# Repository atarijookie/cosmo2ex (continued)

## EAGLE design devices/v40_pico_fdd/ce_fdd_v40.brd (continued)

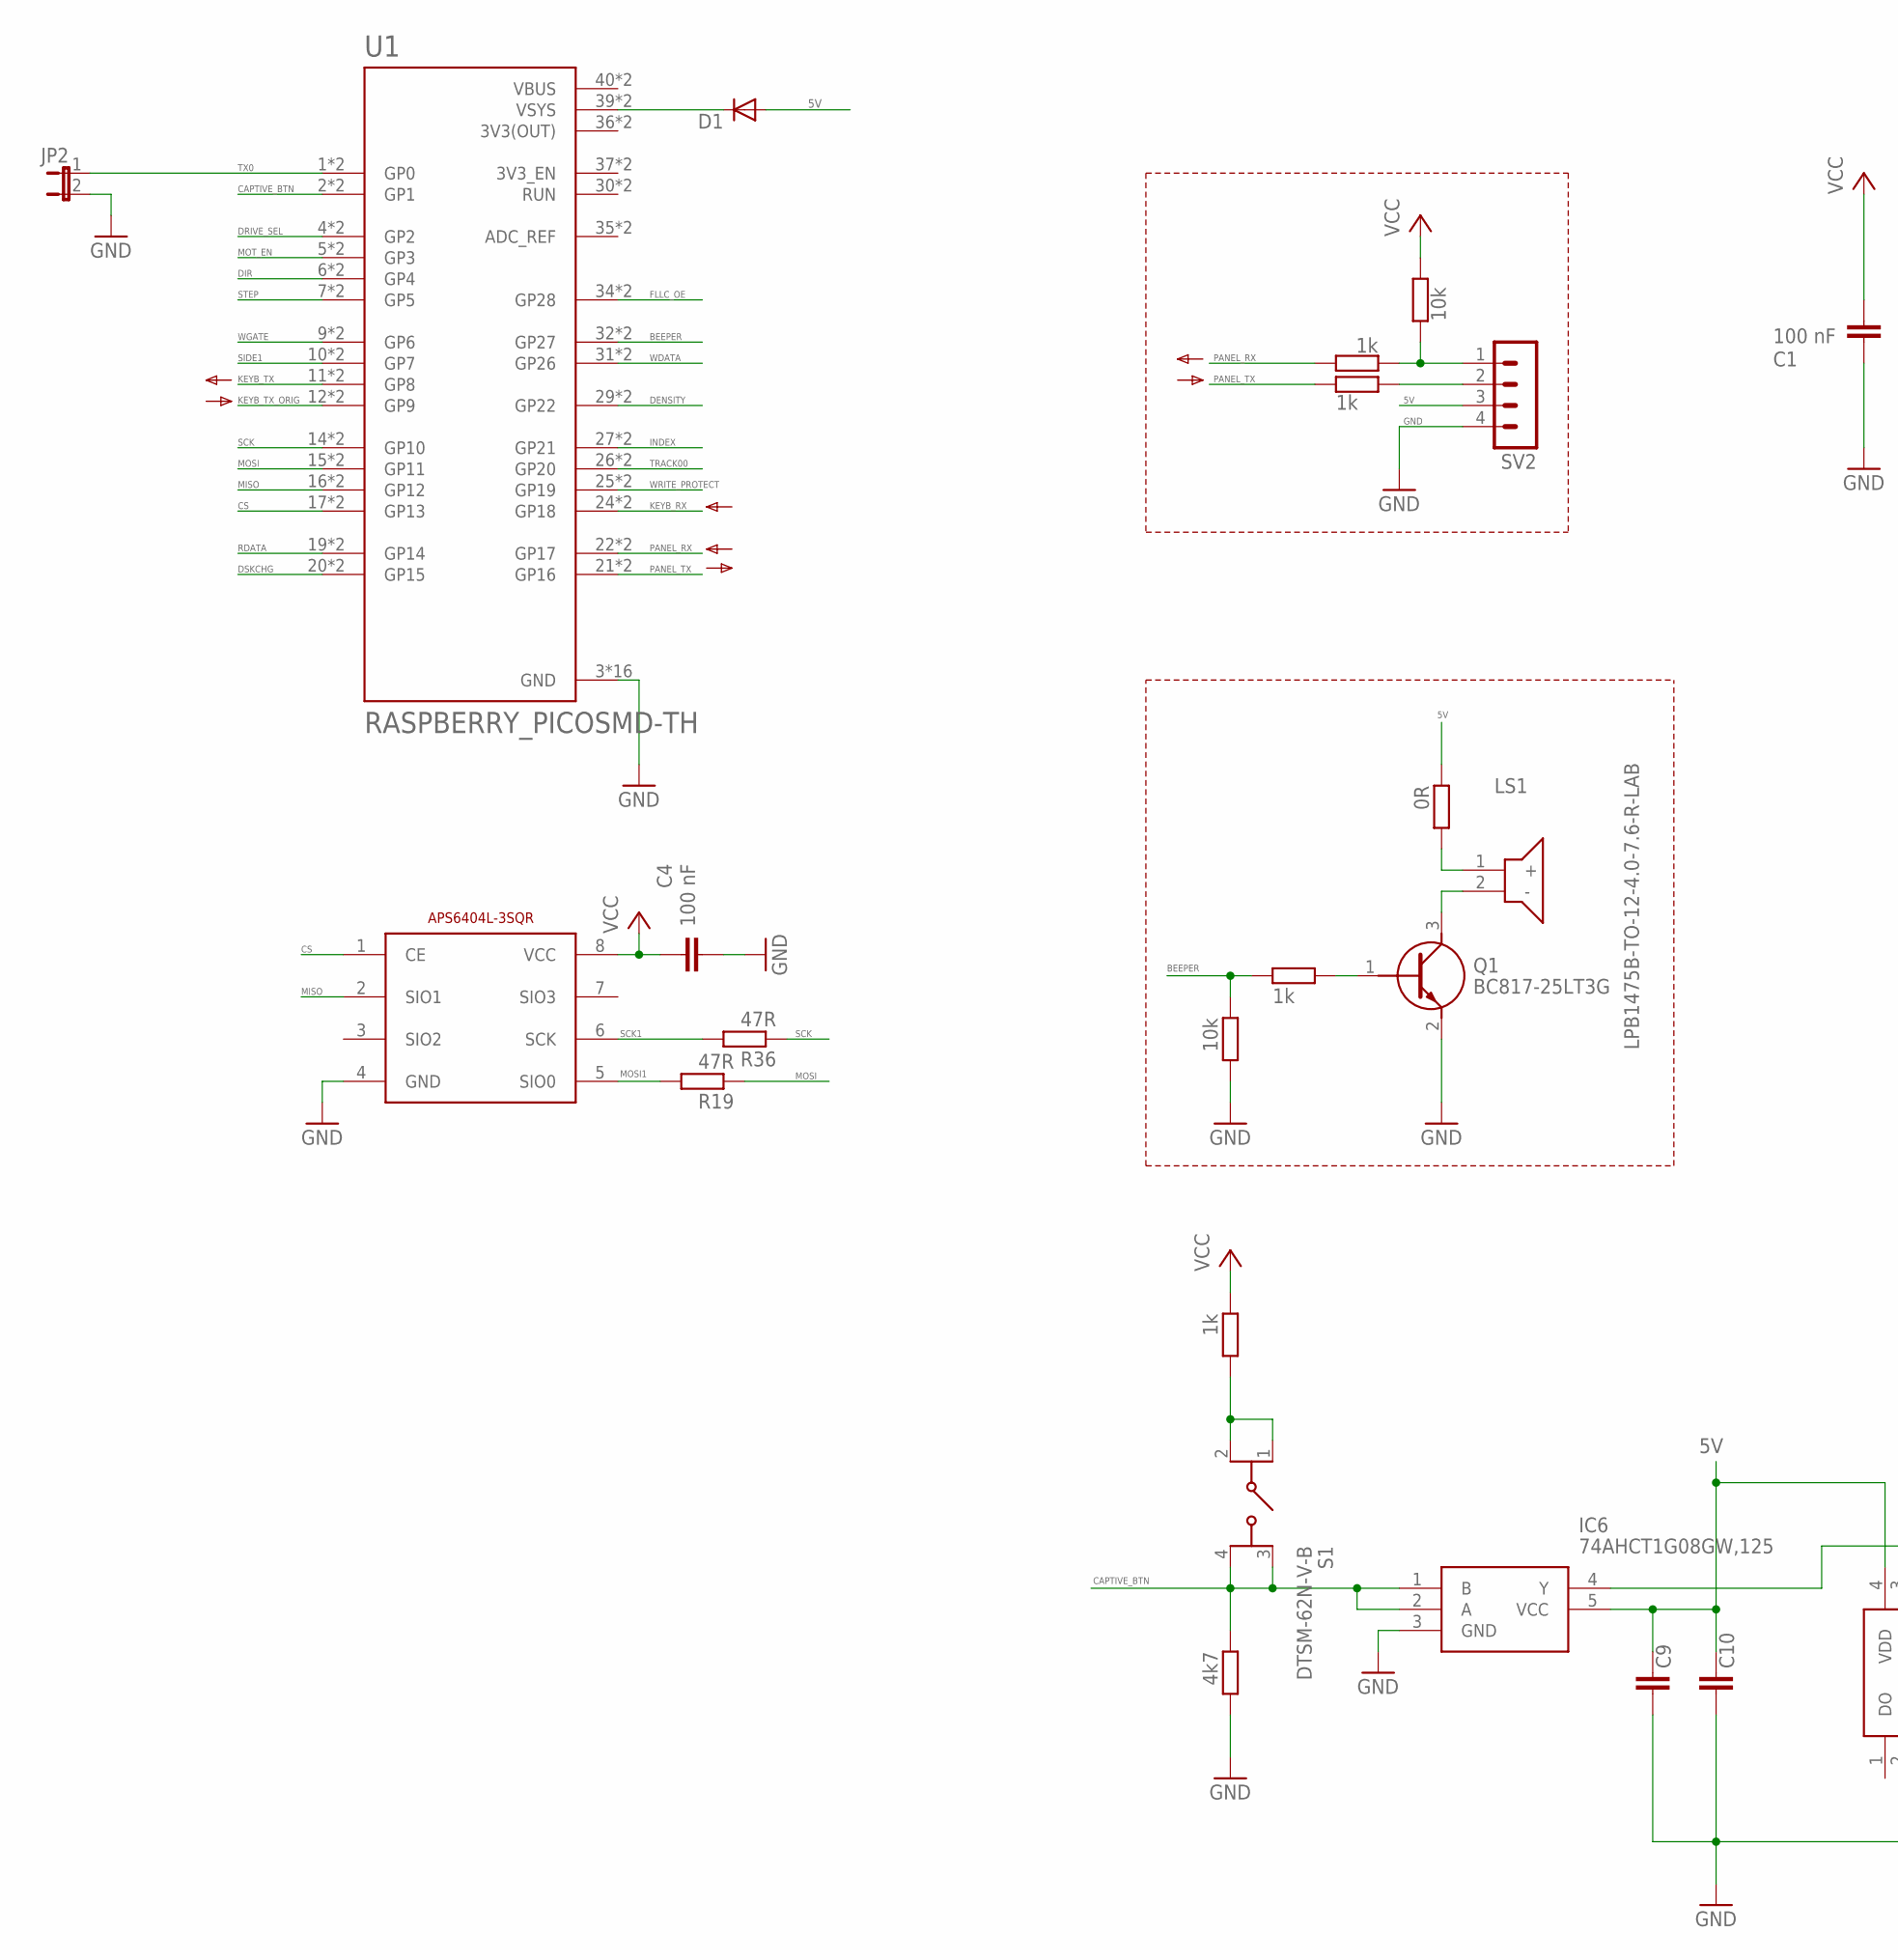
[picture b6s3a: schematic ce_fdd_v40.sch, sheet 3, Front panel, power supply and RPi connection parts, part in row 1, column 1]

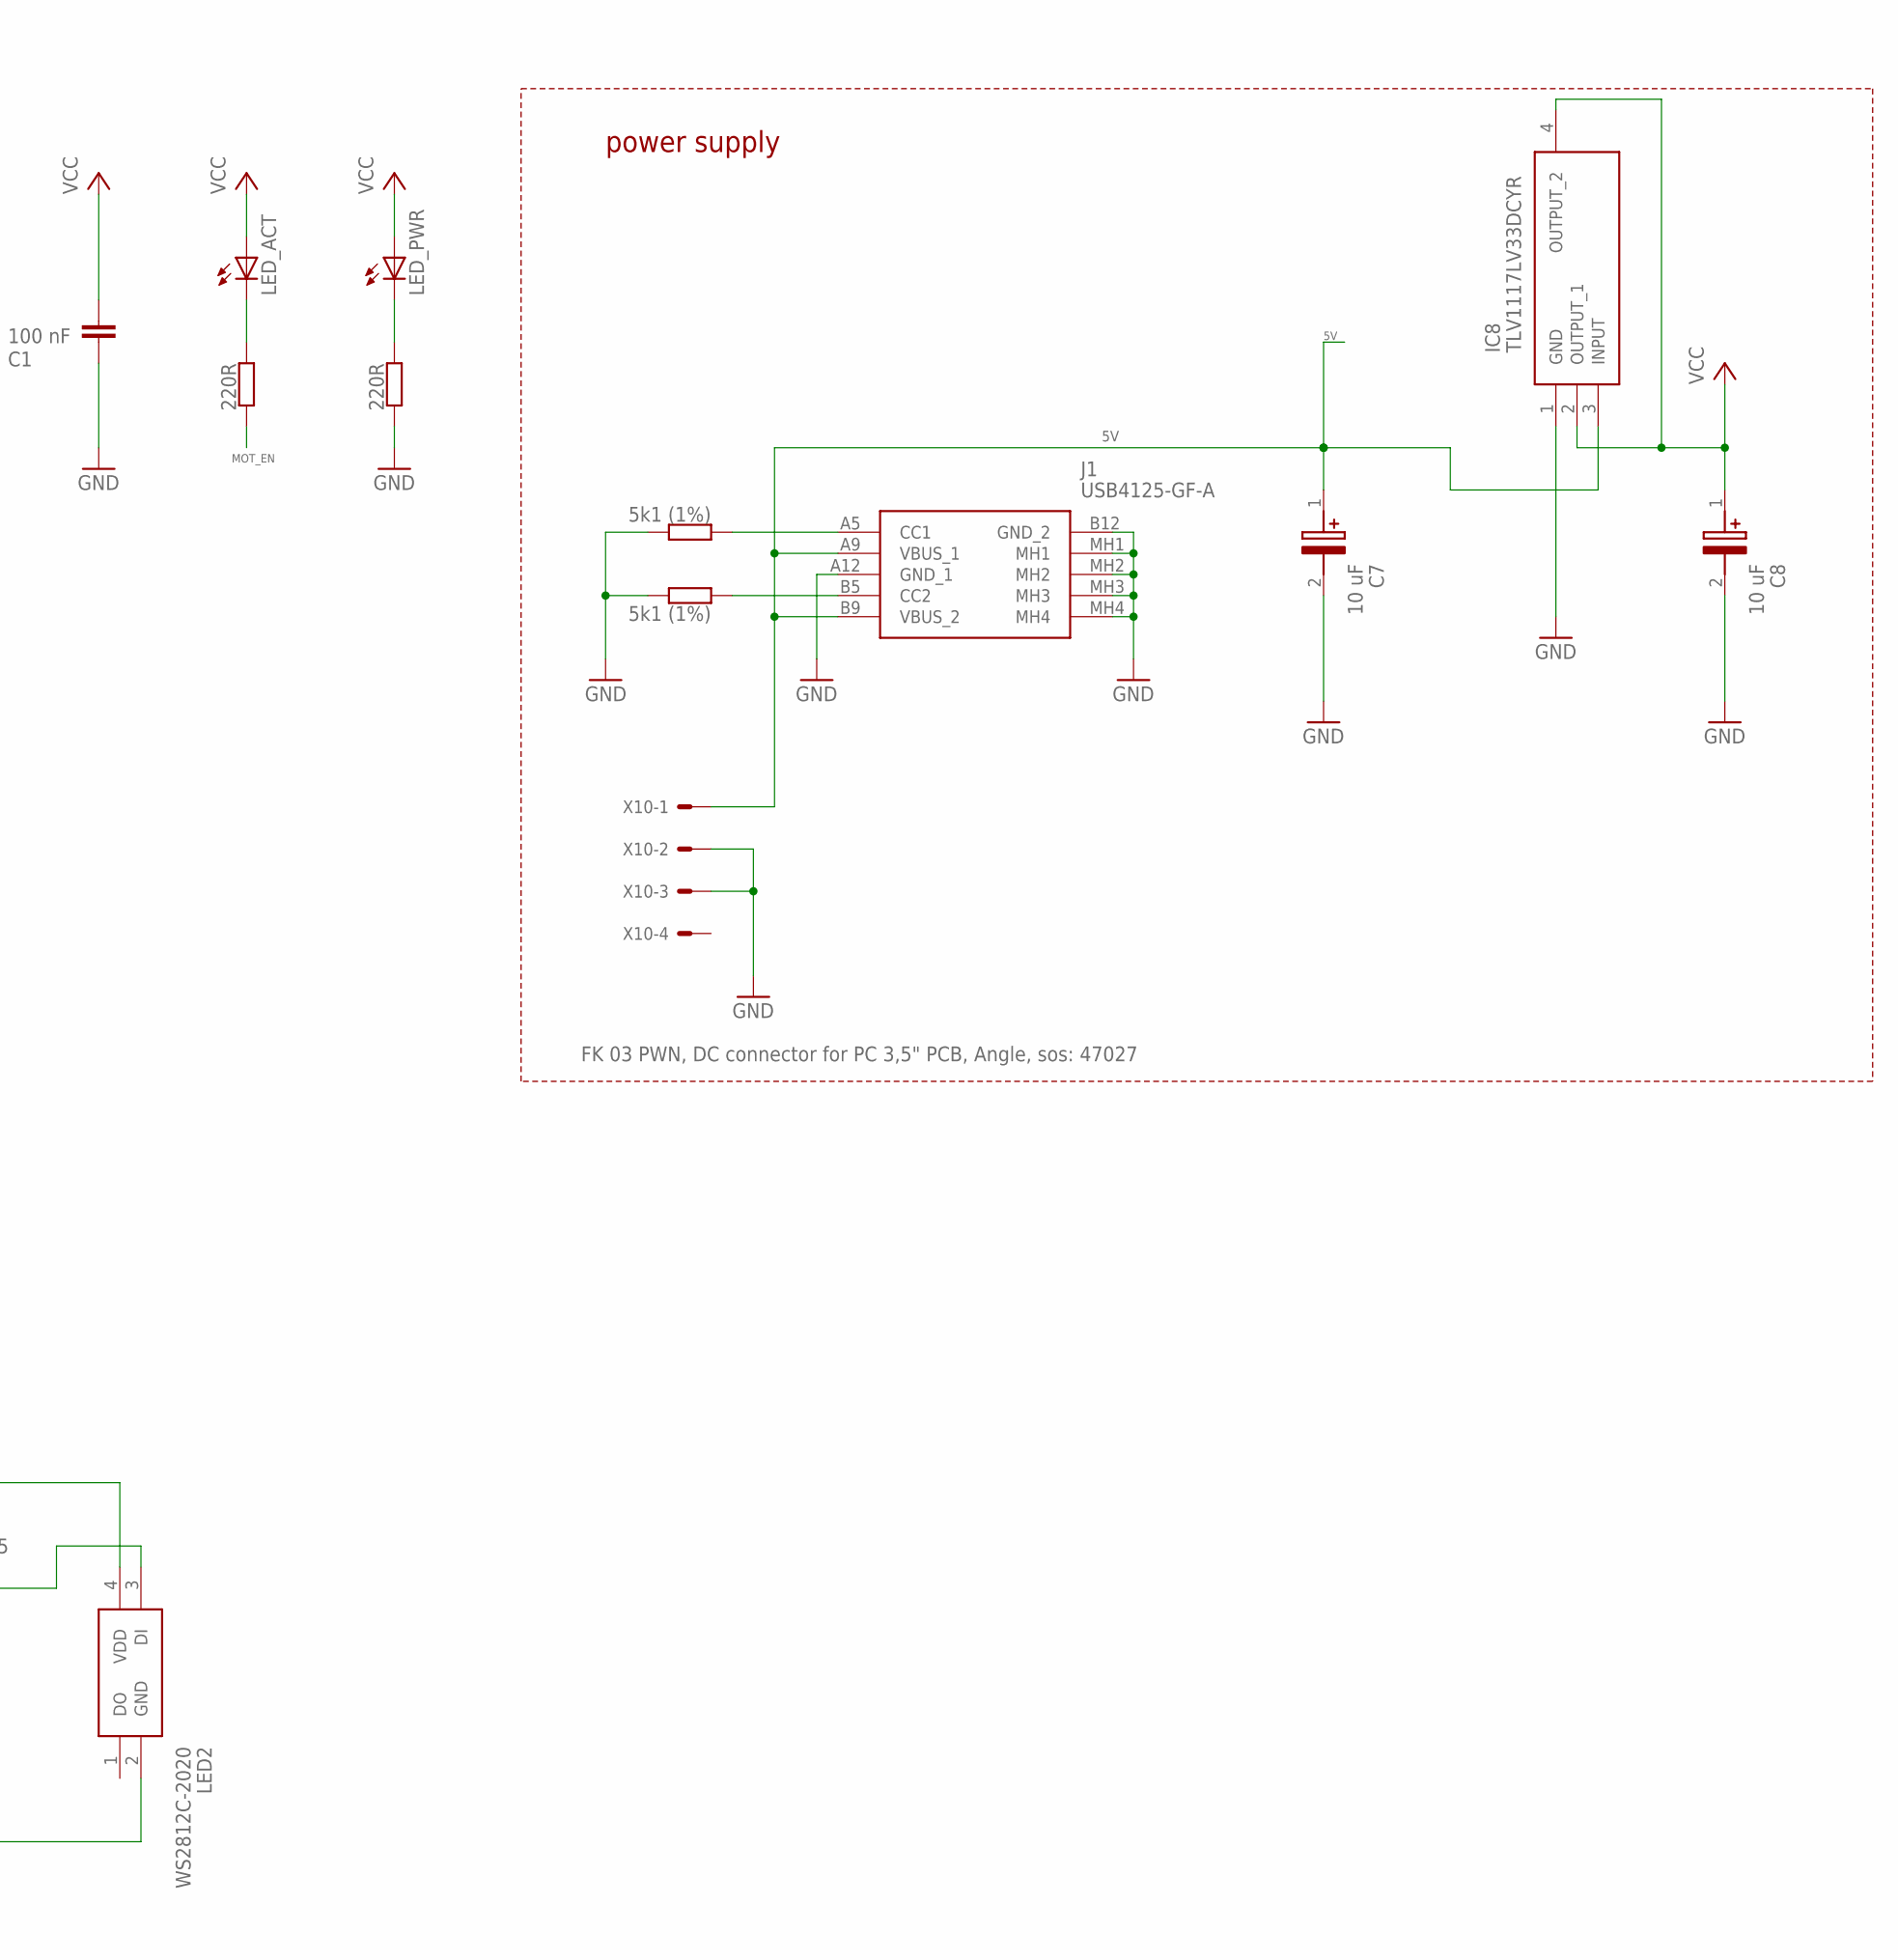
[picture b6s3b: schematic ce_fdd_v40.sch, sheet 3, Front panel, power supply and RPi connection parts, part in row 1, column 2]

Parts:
C1, C4, C9, C10: 100 nF; C0603
C7, C8: 10 uF; CAPPM3528X210N
D1: SK110-DIO; DO214AC
IC6: 74AHCT1G08GW,125; SOT65P212X110-5N
IC8: TLV1117LV33DCYR; SOT230P700X180-4N
J1: USB4125-GF-A; USB4125GFA
JP2: JP1E; JP1
LED2: WS2812C-2020; WS2812C2020
LED_ACT: LEDSML0603; SML0603
LED_PWR: LEDSML0603; SML0603
LS1: LPB1475B-TO-12-4.0-7.6-R-LAB; LPB1475BTO124076RLAB
Q1: BC817-25LT3G; SOT96P237X111-3N
R5: 0R; R0603
R14, R17: 5k1 (1%); R0603
R18, R35: 220R; R0603
R19, R36: 47R; R0603
R20, R30, R32, R37: 1k; R0603
R21, R31: 10k; R0603
R38: 4k7; R0603
S1: DTSM-62N-V-B; DTSM62NVB
SV2: MA04-1
U1: RASPBERRY_PICOSMD-TH; PICO-PKG
U$2: APS6404L-3SQR; SOP-8L
X10: FK 03 PWN, DC connector for PC 3,5" PCB, Angle, s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; 7395-04

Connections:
3V3(OUT): U1.36 (3V3(OUT)), U1.P$36 (3V3(OUT))
5V: C7.1 (+), C9.1, C10.1, D1.A, IC6.5 (VCC), IC8.3 (INPUT), J1.A9 (VBUS_1), J1.B9 (VBUS_2), LED2.4 (VDD), R5.1, SV2.3, X10.1; also elsewhere on the board
BEEPER: R30.1, R31.1, U1.32 (GP27), U1.P$32 (GP27)
CAPTIVE_BTN: IC6.1 (B), IC6.2 (A), R38.1, S1.3 (NO_1), S1.4 (NO_2), U1.2 (GP1), U1.P$2 (GP1)
CS: U1.17 (GP13), U1.P$17 (GP13), U$2.1 (CE)
DENSITY: U1.29 (GP22), U1.P$29 (GP22); also elsewhere on the board
DIR: U1.6 (GP4), U1.P$6 (GP4); also elsewhere on the board
DRIVE_SEL: U1.4 (GP2), U1.P$4 (GP2); also elsewhere on the board
DSKCHG: U1.20 (GP15), U1.P$20 (GP15); also elsewhere on the board
FLLC_OE: U1.34 (GP28), U1.P$34 (GP28); also elsewhere on the board
GND: C1.2, C4.1, C7.2 (-), C8.2 (-), C9.2, C10.2, IC6.3 (GND), IC8.1 (GND), J1.A12 (GND_1), J1.B12 (GND_2), J1.MH1, J1.MH2, J1.MH3, J1.MH4, JP2.2, LED2.2 (GND), Q1.2 (E), R14.2, R17.2, R18.2, R31.2, R38.2, SV2.4, U1.3 (GND), U1.8 (GND), U1.13 (GND), U1.18 (GND), U1.23 (GND), U1.28 (GND), U1.33 (GND), U1.38 (GND), U1.P$3 (GND), U1.P$8 (GND), U1.P$13 (GND), U1.P$18 (GND), U1.P$23 (GND), U1.P$28 (GND), U1.P$33 (GND), U1.P$38 (GND), U$2.4 (GND), X10.2, X10.3; also elsewhere on the board
INDEX: U1.27 (GP21), U1.P$27 (GP21); also elsewhere on the board
KEYB_RX: U1.24 (GP18), U1.P$24 (GP18); also elsewhere on the board
KEYB_TX: U1.11 (GP8), U1.P$11 (GP8); also elsewhere on the board
KEYB_TX_ORIG: U1.12 (GP9), U1.P$12 (GP9); also elsewhere on the board
MISO: U1.16 (GP12), U1.P$16 (GP12), U$2.2 (SIO1)
MOSI: R19.1, U1.15 (GP11), U1.P$15 (GP11)
MOSI1: R19.2, U$2.5 (SIO0)
MOT_EN: R35.2, U1.5 (GP3), U1.P$5 (GP3); also elsewhere on the board
unnamed: J1.B5 (CC2), R14.1
unnamed: J1.A5 (CC1), R17.1
unnamed: Q1.1 (B), R30.2
unnamed: LS1.2 (-), Q1.3 (C)
unnamed: LED_ACT.C, R35.1
unnamed: LED_PWR.C, R18.1
unnamed: LS1.1 (+), R5.2
unnamed: R21.1, R32.1, SV2.1
unnamed: R37.2, SV2.2
unnamed: R20.2, S1.1 (COM_1), S1.2 (COM_2)
unnamed: IC6.4 (Y), LED2.3 (DI)
unnamed: D1.C, U1.39 (VSYS), U1.P$39 (VSYS)
PANEL_RX: R32.2, U1.22 (GP17), U1.P$22 (GP17)
PANEL_TX: R37.1, U1.21 (GP16), U1.P$21 (GP16)
RDATA: U1.19 (GP14), U1.P$19 (GP14); also elsewhere on the board
SCK: R36.1, U1.14 (GP10), U1.P$14 (GP10)
SCK1: R36.2, U$2.6 (SCK)
SIDE1: U1.10 (GP7), U1.P$10 (GP7); also elsewhere on the board
STEP: U1.7 (GP5), U1.P$7 (GP5); also elsewhere on the board
TRACK00: U1.26 (GP20), U1.P$26 (GP20); also elsewhere on the board
TX0: JP2.1, U1.1 (GP0), U1.P$1 (GP0)
VBUS: U1.40 (VBUS), U1.P$40 (VBUS)
VCC: C1.1, C4.2, C8.1 (+), IC8.2 (OUTPUT_1), IC8.4 (OUTPUT_2), LED_ACT.A, LED_PWR.A, R20.1, R21.2, U$2.8 (VCC); also elsewhere on the board
WDATA: U1.31 (GP26), U1.P$31 (GP26); also elsewhere on the board
WGATE: U1.9 (GP6), U1.P$9 (GP6); also elsewhere on the board
WRITE_PROTECT: U1.25 (GP19), U1.P$25 (GP19); also elsewhere on the board

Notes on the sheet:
power supply

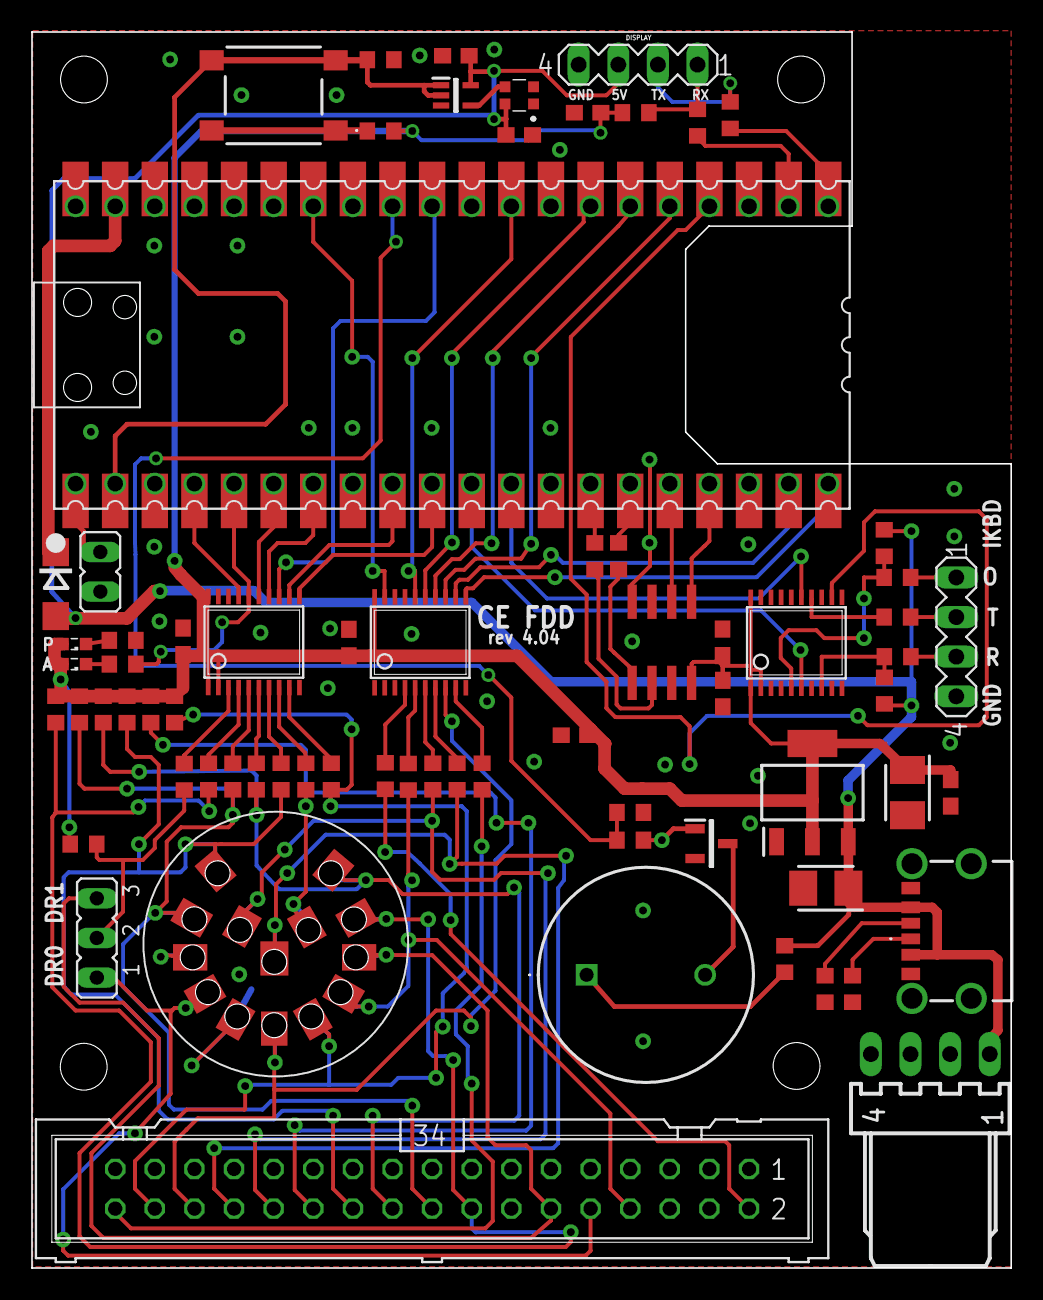
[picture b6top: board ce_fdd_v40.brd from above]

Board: 2 copper layers, 62.8 x 79.2 mm, 71 parts (0 on the bottom side), 78 nets.

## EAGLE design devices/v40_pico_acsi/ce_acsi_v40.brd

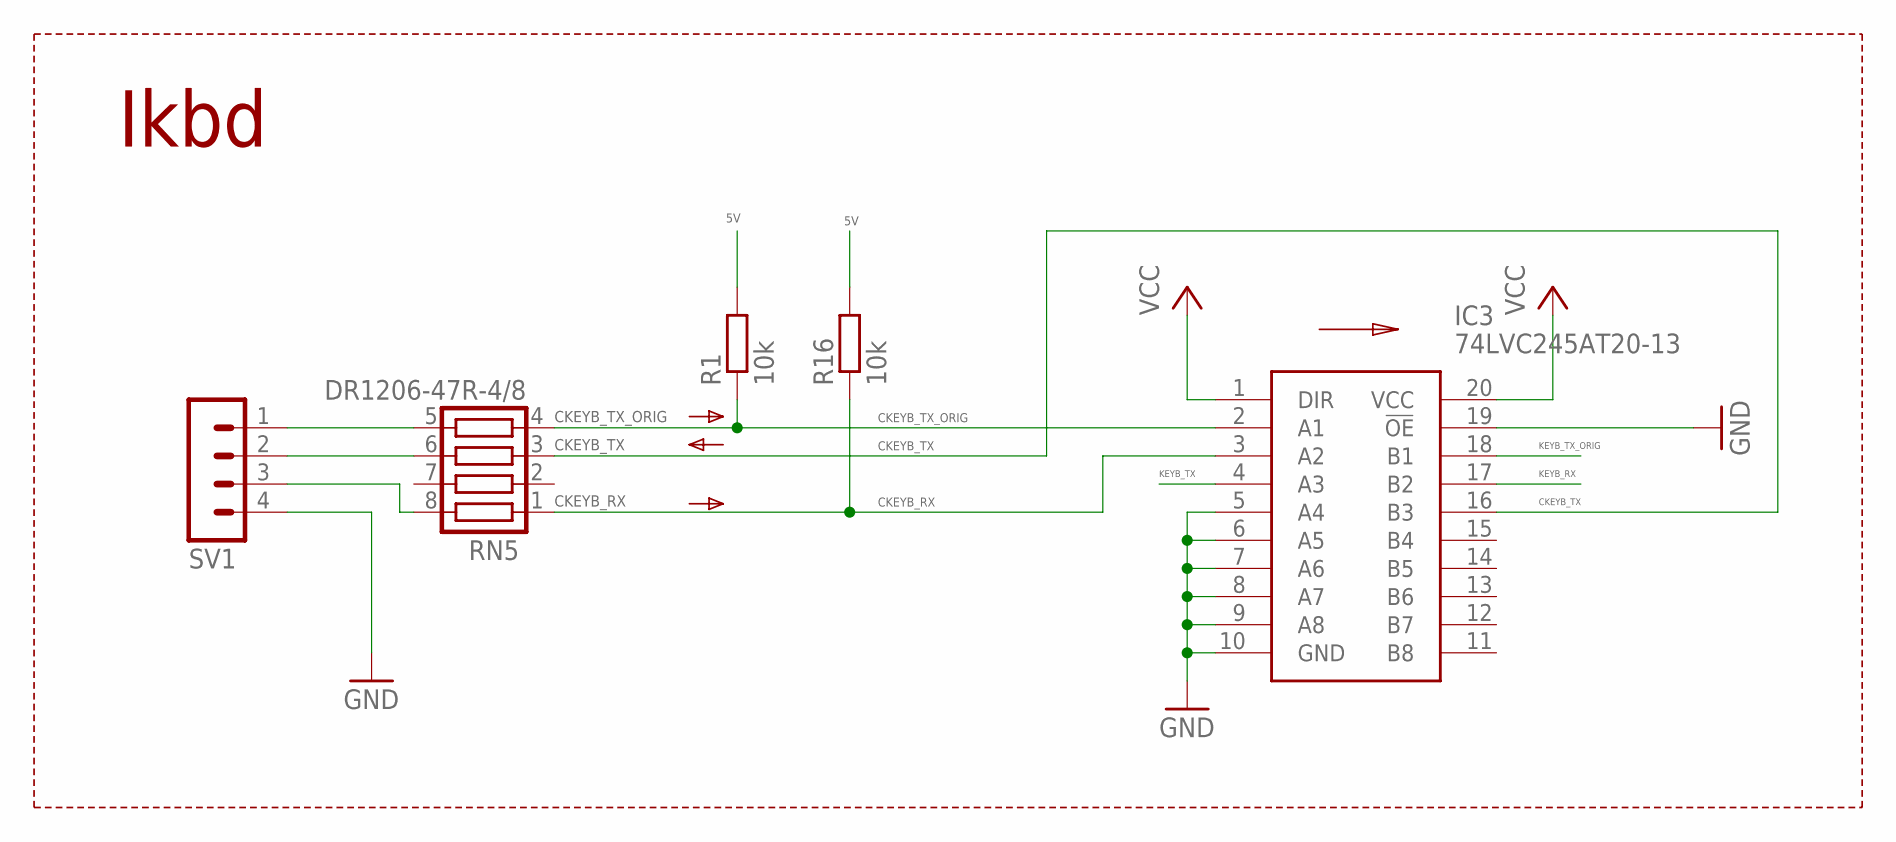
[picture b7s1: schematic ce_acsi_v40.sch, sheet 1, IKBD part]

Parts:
IC3: 74LVC245AT20-13; SOP65P640X120-20N
R1, R16: 10k; R0603
RN5: DR1206-47R-4/8; CTS742C083
SV1: MA04-1

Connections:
5V: R1.2, R16.2; also elsewhere on the board
CKEYB_RX: IC3.3 (A2), R16.1, RN5.1
CKEYB_TX: IC3.16 (B3), RN5.3
CKEYB_TX_ORIG: IC3.2 (A1), R1.1, RN5.4
GND: IC3.5 (A4), IC3.6 (A5), IC3.7 (A6), IC3.8 (A7), IC3.9 (A8), IC3.10 (GND), IC3.19 (!OE), SV1.4; also elsewhere on the board
KEYB_RX: IC3.17 (B2); also elsewhere on the board
KEYB_TX: IC3.4 (A3); also elsewhere on the board
KEYB_TX_ORIG: IC3.18 (B1); also elsewhere on the board
unnamed: RN5.6, SV1.2
VCC: IC3.1 (DIR), IC3.20 (VCC); also elsewhere on the board
ZKEYB_RX: RN5.8, SV1.3
ZKEYB_TX_ORIG: RN5.5, SV1.1

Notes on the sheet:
Ikbd

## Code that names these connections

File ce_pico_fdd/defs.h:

#ifndef DEFS_H_
#define DEFS_H_

#include <cstdint>

#define DEBUG_STRINGS   1       // debug() on GP0 (TX0), 115200 baud; 0 = no output, see debug() in utils.cpp
#ifndef MFM_PERF_TEST
#define MFM_PERF_TEST   0       // 1 = track stream timing test next to the real stream, results in the debug log every 5 s, see mfm_perf.h
#endif
#ifndef BUILTIN_IMAGE_TEST
#define BUILTIN_IMAGE_TEST 0    // 1 = the built-in floppy shows all its statuses in a loop (sample values, BUILTIN_TEST_STEP_MS each, then
#endif                          //     no status sector for a step) and never switches to the real image - see builtin_image.h
#define BUILTIN_TEST_STEP_MS 8000
#define FDD_STATUS_LOG  0       // 1 = floppy status in the debug log once a second while the ST uses the drive, see core1StatusReport()

#ifndef TRUE
    #define TRUE 1
#endif

#ifndef FALSE
    #define FALSE 0
#endif

#ifndef MIN
    #define MIN(X,Y)    ((X < Y) ? X : Y)
#endif

#ifndef MAX
    #define MAX(X,Y)    ((X > Y) ? X : Y)
#endif

#define MFM_4US         1
#define MFM_6US         2
#define MFM_8US         3

#define DEV_FEATURE_IKBD    8
#define DEV_FEATURE_FDD     4
#define DEV_FEATURE_SCSI    2
#define DEV_FEATURE_ACSI    1

// commands sent from device to host
#define ATN_FW_VERSION          0x01        // followed by string with FW version (length: 4 WORDs - cmd, v[0], v[1], 0)
#define ATN_SECTOR_WRITTEN      0x03        // sent: 3, side (highest bit) + track #, current sector #
#define ATN_SEND_TRACK          0x04        // send the whole track
#define ATN_SEND_WHOLE_IMAGE    0x05        // send the whole image
#define ATN_GET_IMAGE_LIST      0x06        // page of image names in the folder of the current image - see image_browser.h
#define ATN_INSERT_IMAGE        0x07        // insert image from that folder by name, the host replies with INSERT_IMAGE_*
#define ATN_DEVICE_SETTINGS     0x08        // host -> device only: settings flags (1 B, DEV_SETTING_* in settings.h) from the web UI
#define ATN_LED_COLORS          0x09        // host -> device only: neopixel color while running - R, G, B (3 B), from the web UI
#define ATN_FW_INFO             0x0a        // identity, size + MD5 of the running image, FS position - once per connection, see fw_update.cpp
#define ATN_FW_UPDATE_STATUS    0x0b        // answer to each CMD_FW_UPDATE_* - see fw_update.cpp

// firmware update (OTA) from the web UI, host -> device - the same codes as on HDD, see fw_update.cpp
#define CMD_FW_UPDATE_START     0xf0        // image size (4 B), MD5 of the image (16 B)
#define CMD_FW_UPDATE_DATA      0xf1        // offset (4 B), data (max FWU_CHUNK_MAX B)
#define CMD_FW_UPDATE_END       0xf2        // check identity, layout, MD5, then reboot into the OTA stub
#define CMD_FW_UPDATE_ABORT     0xf3

#define INSERT_IMAGE_OK         0           // found, loading - the image follows as on ATN_SEND_WHOLE_IMAGE
#define INSERT_IMAGE_NOT_FOUND  1           // no such image in the folder (anymore)
#define INSERT_IMAGE_FAILED     2           // bad request, or the current image can't be browsed

// commands sent from host to device
#define CMD_WRITE_PROTECT_OFF       0x10
#define CMD_WRITE_PROTECT_ON        0x20
#define CMD_DISK_CHANGE_OFF         0x30
#define CMD_DISK_CHANGE_ON          0x40
#define CMD_GET_FW_VERSION          0x60
#define CMD_SET_DRIVE_ID_0          0x70
#define CMD_SET_DRIVE_ID_1          0x80
#define CMD_CURRENT_TRACK           0x90                            // followed by track #
#define CMD_DRIVE_ENABLED           0xa0
#define CMD_DRIVE_DISABLED          0xb0


///////////////////////////

#define TX_HEADER_SIZE                  10
#define ATN_SENDFWVERSION_LEN_TX        (TX_HEADER_SIZE + 14)       // version (4), features, 0, mac (6), settings flags, 0
#define ATN_SENDTRACK_REQ_LEN_TX        (TX_HEADER_SIZE + 2)

///////////////////////////

#define SPI_PORT spi0

#define PANEL_UART_BAUD     115200


#define PIN_TXD_DEBUG       0
#define PIN_CAPTIVE_BTN     1       // button to 3.3V (H = pressed), long press starts the captive portal - instead of the debug UART RX, which isn't used
#define PIN_NEOPIXEL        1       // the same pin, to LED2 through the AND gate IC6 - output only while sending a frame, see neopixel_pio.cpp
#define PIN_DRIVE_SEL       2
#define PIN_MOT_EN          3
#define PIN_DIR             4
#define PIN_STEP            5
#define PIN_WGATE           6
#define PIN_SIDE1           7
#define PIN_KEYB_TX         8
#define PIN_KEYB_TX_ORIG    9
#define PIN_SCK             10
#define PIN_MOSI            11
#define PIN_MISO            12
#define PIN_CS              13
#define PIN_RDATA           14
#define PIN_DSKCHG          15
#define PIN_PANEL_TX        16      // front panel UART (PIO), see ce_pico_display/protocol.md
#define PIN_PANEL_RX        17
#define PIN_KEYB_RX         18
#define PIN_WPROTECT        19
#define PIN_TRACK00         20
#define PIN_INDEX           21
#define PIN_DENSITY         22
#define PIN_WDATA           26
#define PIN_BEEPER          27      // buzzer with its own generator, H = on, see beeper.h
#define PIN_FLCC_OE         28

#define BIT_IS_H(PIN)   (gpio_get(PIN) != 0)
#define BIT_IS_L(PIN)   (gpio_get(PIN) == 0)
#define BIT_LEVEL(PIN)  ( (gpio_get(PIN) == 0) ? 0 : 1)

#define WRITEBUFFER_SIZE    1300

typedef struct {
    volatile uint8_t side;
    volatile uint8_t track;
    volatile uint8_t sector;
} TDrivePosition;

#define READTRACKDATA_SIZE_BYTES    13800
#define MAX_TRACKS                  90
#define MAX_SECTORS_PER_TRACK       11

#define IMAGE_NOT_LOADED    0
#define IMAGE_REQUESTED     1
#define IMAGE_LOADED        2

#define TAG_WRITE_START 0x80    // start of sector data - sent from MFM streamer
#define TAG_WRITE_END   0xc0    // end of sector data - sent from MFM streamer

#endif /* DEFS_H_ */

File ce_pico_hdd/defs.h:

#ifndef DEFS_H_
#define DEFS_H_

#include <Arduino.h>

#define LOG_MORE    1
#define LOG_LED     1
// #define LOG_UART    1

// LOG_LED debug output goes to the LED pin (GP25) of the W6100-EVB-Pico by default.
// It goes to GP22 (KEYB_TX, J1 pin 2) at 115200 baud instead, with the IKBD functionality off, when:
//   - the debug dongle (J1 pin 2 shorted to J1 pin 3) is detected on boot - see debugDongleDetect() in utils.cpp, or
//   - DEBUG_TO_IKBD is 1 - forced, without the dongle.
#ifndef DEBUG_TO_IKBD
    #define DEBUG_TO_IKBD   0
#endif

#ifndef MIN
    #define MIN(X,Y)    ((X < Y) ? X : Y)
#endif

#ifndef MAX
    #define MAX(X,Y)    ((X > Y) ? X : Y)
#endif

#define DEV_FEATURE_IKBD    8
#define DEV_FEATURE_FDD     4
#define DEV_FEATURE_SCSI    2
#define DEV_FEATURE_ACSI    1

#define CMD_TIMEOUT_SECS_PER_MB 3
#define CMD_TIMEOUT_ONESECOND   1000
#define CMD_TIMEOUT_SHORT       (CMD_TIMEOUT_ONESECOND / 2)     // this period will be 0.5 second
#define CMD_TIMEOUT_LONG        (CMD_TIMEOUT_ONESECOND * 3)     // this period will be 3.0 second

// commands sent from device to host
#define ATN_FW_VERSION                      0x01                                // followed by string with FW version (length: 4 uint16_ts - cmd, v[0], v[1], 0)
#define ATN_ACSI_COMMAND                    0x02
// #define ATN_READ_MORE_DATA                  0x03
#define ATN_WRITE_MORE_DATA                 0x04
// #define ATN_GET_STATUS                      0x05
#define ATN_FW_INFO                         0x0a    // identity, size + MD5 of the running image, FS position - once per connection, see fw_update.cpp
#define ATN_FW_UPDATE_STATUS                0x0b    // answer to each CMD_FW_UPDATE_* - see fw_update.cpp

// commands sent from host to device
#define CMD_ACSI_CONFIG                     0x10
#define CMD_DATA_WRITE                      0x20
#define CMD_DATA_READ_WITH_STATUS           0x30
#define CMD_SEND_STATUS                     0x40
#define CMD_DATA_READ_WITHOUT_STATUS        0x50
#define CMD_FLOPPY_CONFIG                   0x70
#define CMD_FLOPPY_SWITCH                   0x80
#define CMD_DATA_MARKER                     0xda
#define CMD_LED_COLORS                      0xe0    // neopixel colors while running: ACSI R, G, B, SCSI R, G, B (6 B), from the web UI

// firmware update (OTA) from the web UI - see fw_update.cpp; the device answers each with ATN_FW_UPDATE_STATUS
#define CMD_FW_UPDATE_START                 0xf0    // image size (4 B), MD5 of the image (16 B)
#define CMD_FW_UPDATE_DATA                  0xf1    // offset (4 B), data (max FWU_CHUNK_MAX B)
#define CMD_FW_UPDATE_END                   0xf2    // check identity, layout, MD5, then reboot into the OTA stub
#define CMD_FW_UPDATE_ABORT                 0xf3

// ACSI only - for the SLM laser printer emulation on host (ce_cores/hdd/slm/)
#define CMD_PIO_READ                        0x90    // send the payload bytes to ST with CS / INT handshake (status + EXTENDED STATUS PHASE), then wait for next command
#define CMD_PIO_WRITE                       0xc0    // get N bytes from ST with CS / INT handshake (EXTENDED COMMAND PHASE), sent to host as on DMA write
#define CMD_DATA_WRITE_PACED                0xd0    // DMA write in printer scan line bursts, see onDataWritePaced()
#define DATA_WRITE_PACED_PAYLOAD_SIZE       16

// these states define if the device should get command or transfer data
#define STATE_GET_COMMAND                       0
// #define STATE_SEND_COMMAND                   1
#define STATE_WAIT_COMMAND_RESPONSE             2
#define STATE_DATA_READ_WITH_STATUS             3
#define STATE_DATA_READ_WITHOUT_STATUS          4
#define STATE_DATA_WRITE                        5
#define STATE_WAIT_FOR_STATUS_ARRIVAL           6
#define STATE_READ_STATUS                       7

#define STATE_SEND_FW_VER                       10
#define STATE_SEND_WRITE_MORE_DATA              11
#define STATE_DATA_READ                         12
#define STATE_PIO_READ                          13
#define STATE_PIO_WRITE                         14
#define STATE_DATA_WRITE_PACED                  15

///////////////////////////

#define ATN_VARIABLE_LEN                0xffff

#define TX_HEADER_SIZE                  10
#define ATN_SENDFWVERSION_LEN_TX        (TX_HEADER_SIZE + 12)
#define ATN_SENDACSICOMMAND_LEN_TX      (TX_HEADER_SIZE + 14)

///////////////////////////
// pins of the v40_pico_hdd board (devices/v40_pico_hdd) - one PCB, assembled either as ACSI or as SCSI variant.
// Most of the GPIOs have a different function in each variant, the variant is read from PIN_VARIANT_STRAP on boot.

// common for both variants
#define PIN_D0              0       // D0..D7 through IC2/IC3 (both variants), DATA_DIR sets their direction
#define PIN_D1              1
#define PIN_D2              2
#define PIN_D3              3
#define PIN_D4              4
#define PIN_D5              5
#define PIN_D6              6
#define PIN_D7              7
#define PIN_ACK             10      // in  - SCSI: CACK (through latch IC203), ACSI: ACK (through IC101)
#define PIN_DATA_DIR        28      // out

#define PIN_NEOPIXEL        9       // out - ACSI only: to the WS2812 through the AND gate IC6 (5V level shifter), its other input is H (R151).
                                    //       SCSI: the neopixel data is OUT_LE1 on IC6.A, gated by OUT_LE2 on IC6.B
#define PIN_VARIANT_STRAP   26      // in on boot - H: ACSI (R125 pull-up), L: SCSI (R225 pull-down)

#define PIN_KEYB_RX         15
#define PIN_KEYB_TX         22
#define PIN_KEYB_TX_ORIG    27

#define PIN_DEBUG_TX_LED    25          // LOG_LED debug output by default - the LED pin of the module, not on its edge pins
                                        // (with the debug dongle / DEBUG_TO_IKBD it's PIN_KEYB_TX instead, see debugToIkbd)

// SCSI variant
#define PIN_SEL_IO_DP_DS    8
#define PIN_RST_CD_REQ_CP   9
#define PIN_IN_OE           11      // out
#define PIN_OUT_OE          12      // out
#define PIN_OUT_LE1         13      // out
#define PIN_OUT_LE2         14      // out
#define PIN_ATN_MSG         26

// ACSI variant
#define PIN_A1              8       // in
#define PIN_CS              11      // in
#define PIN_INT             12      // out
#define PIN_DRQ             13      // out
#define PIN_RESET           14      // in

#define DATA_PINS_MASK          ((1 << PIN_D0) | (1 << PIN_D1) | (1 << PIN_D2) | (1 << PIN_D3) | (1 << PIN_D4) | (1 << PIN_D5) | (1 << PIN_D6) | (1 << PIN_D7))
#define SCSI_DATA_PINS_MASK     (DATA_PINS_MASK | (1 << PIN_SEL_IO_DP_DS))      // data + DP
#define SCSI_HANDSHAKE_PINS_MASK    ((1 << PIN_RST_CD_REQ_CP) | (1 << PIN_ACK))
#define ACSI_HANDSHAKE_OUT_PINS     ((1 << PIN_DRQ) | (1 << PIN_INT))

#define BIT_IS_H(PIN)   (gpio_get(PIN) != 0)
#define BIT_IS_L(PIN)   (gpio_get(PIN) == 0)
#define BIT_LEVEL(PIN)  ( (gpio_get(PIN) == 0) ? 0 : 1)

#define BIT_SET(PIN)    gpio_put(PIN, true)
#define BIT_CLR(PIN)    gpio_put(PIN, false)

#endif /* DEFS_H_ */

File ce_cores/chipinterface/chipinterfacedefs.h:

#ifndef __CHIPINTERFACEDEFS_H__
#define __CHIPINTERFACEDEFS_H__

#include <stdint.h>
#include <sys/socket.h>
#include <netinet/in.h>

// types of chip interface, as returned by the individual chip interface classes
#define CHIP_IF_DUMMY   -1
#define CHIP_IF_V1_V2   1
#define CHIP_IF_V3      3
#define CHIP_IF_V4      4
#define CHIP_IF_RASCSI  8
#define CHIP_IF_NETWORK 9

//---------------------------------------------
// ATN codes: commands sent from device to host (in header, see BufferedReader)

#define ATN_ANY                         0xff        // this is used only on host to wait for any ATN

// Hans (HDD)
#define ATN_FW_VERSION                  0x01        // followed by FW version, mac, features (shared with Franz, same code)
#define ATN_ACSI_COMMAND                0x02
#define ATN_READ_MORE_DATA              0x03
#define ATN_WRITE_MORE_DATA             0x04
// ATN_GET_STATUS                       0x05        // not used by current firmware

// Franz (FDD) - ATN_FW_VERSION (0x01) as above
#define ATN_SECTOR_WRITTEN              0x03        // sent: 3, side (highest bit) + track #, current sector #
#define ATN_SEND_TRACK                  0x04        // send the whole track
#define ATN_SEND_WHOLE_IMAGE            0x05        // send the whole image
#define ATN_GET_IMAGE_LIST              0x06        // page of image names in the folder of the current image, see fdd/imagelist.h
                                                    //   device: start (4 B, 0xffffffff = around the current image), count (2 B)
                                                    //   host (the reply, and on its own when the list / current image changes):
                                                    //   gen, total, current index, start (4 B each), count (2 B), count * [len (1 B), name]
#define ATN_INSERT_IMAGE                0x07        // insert image from that folder by name
                                                    //   device: gen, index (4 B each), name len (1 B), name
                                                    //   host: status (1 B) - INSERT_IMAGE_*

#define ATN_DEVICE_SETTINGS             0x08        // host -> device only: settings flags (1 B, DEV_SETTING_*) changed in the web UI;
                                                    //   the device reports its flags in the FW report (byte 12 of the data)

#define ATN_LED_COLORS                  0x09        // host -> device only: neopixel color while running - R, G, B (3 B), from the web UI
                                                    //   (global settings, LED_COLOR_SETTING_*); sent once per connection and on change

// HDD and FDD - firmware info and update (OTA), see FwUpdateSender (fwupdatesender.h) and ce_pico_hdd/fw_update.cpp
#define ATN_FW_INFO                     0x0a        // once per connection, after the FW version: image size (4 B), MD5 of the image (16 B),
                                                    //   FS start, FS end (4 B each, offsets in flash), flags (1 B, bit 0: OTA possible,
                                                    //   bit 1: new firmware on trial, bit 2: rolled back to the previous firmware), 0,
                                                    //   identity "dev=HDD;type=W6100-EVB-PICO;chip=RP2040;build=v1.0.0;" (zero terminated)
#define ATN_FW_UPDATE_STATUS            0x0b        // answer to each CMD_FW_UPDATE_*: cmd (1 B), result (1 B, 0 = OK), received (4 B), message

#define DEV_SETTING_IKBD                0x01        // device IKBD (keyboard / mouse via the host) enabled
#define DEV_SETTING_BEEP_ON_STEP        0x02        // beeper clicks on every head step

#define INSERT_IMAGE_OK                 0           // found, loading - the image follows as on ATN_SEND_WHOLE_IMAGE
#define INSERT_IMAGE_NOT_FOUND          1           // no such image in the folder (anymore)
#define INSERT_IMAGE_FAILED             2           // bad request, or the current image can't be browsed (no image, special image)

//---------------------------------------------
// CMD codes: commands sent from host to device

// Hans (HDD)
#define CMD_ACSI_CONFIG                 0x10
#define CMD_DATA_WRITE                  0x20
#define CMD_DATA_READ_WITH_STATUS       0x30
#define CMD_SEND_STATUS                 0x40
#define CMD_DATA_READ_WITHOUT_STATUS    0x50
#define CMD_FLOPPY_CONFIG               0x70
#define CMD_FLOPPY_SWITCH               0x80
#define CMD_GET_LICENSE                 0xa0
#define CMD_DO_UPDATE                   0xb0
#define CMD_DATA_MARKER                 0xda
#define CMD_LED_COLORS                  0xe0        // neopixel colors while running: ACSI R, G, B, SCSI R, G, B (6 B) - the device
                                                    //   uses the one of its variant; sent once per connection and on change
#define CMD_FW_UPDATE_START             0xf0        // firmware update (HDD and FDD), see FwUpdateSender: image size (4 B), MD5 (16 B)
#define CMD_FW_UPDATE_DATA              0xf1        //   offset (4 B), data (max FWU_CHUNK_SIZE)
#define CMD_FW_UPDATE_END               0xf2        //   device checks the image, answers, reboots into the new firmware
#define CMD_FW_UPDATE_ABORT             0xf3

// Hans (HDD) - ACSI only, for the SLM laser printer emulation (hdd/slm/)
#define CMD_PIO_READ                    0x90        // send the payload bytes to ST one by one with CS / INT handshake (status + EXTENDED STATUS PHASE), then wait for the next command; no payload = just wait for the next command
#define CMD_PIO_WRITE                   0xc0        // get N bytes from ST with CS / INT handshake (EXTENDED COMMAND PHASE), N in 24 bits; data comes back as on CMD_DATA_WRITE
#define CMD_DATA_WRITE_PACED            0xd0        // get N bytes from ST using DMA, in bursts of one printer scan line (payload: see ChipInterface::hdd_recvDataPaced_start())
#define DATA_WRITE_PACED_PAYLOAD_SIZE   16
#define PIO_READ_MAX_LEN                64          // device waits for at most this many payload bytes (PAYLOAD_MAX_WAIT_SIZE in ce_pico_hdd)

// Franz (FDD)
#define CMD_WRITE_PROTECT_OFF           0x10
#define CMD_WRITE_PROTECT_ON            0x20
#define CMD_DISK_CHANGE_OFF             0x30
#define CMD_DISK_CHANGE_ON              0x40
#define CMD_SET_DRIVE_ID_0              0x70
#define CMD_SET_DRIVE_ID_1              0x80
#define CMD_DRIVE_ENABLED               0xa0
#define CMD_DRIVE_DISABLED              0xb0

//---------------------------------------------
// sizes

#define COMMAND_SIZE            10
#define ACSI_CMD_SIZE           14
#define WRITTENMFMSECTOR_SIZE   2048
#define TX_RX_BUFF_SIZE         600

// Most of the normal games have tracks from 11000 bytes to 12019 bytes of encoded stream.
// With Bad_Brew_Crew/BBC11.ZIP (11 sectors per track?) the resulting stream was 13205 bytes big, I didn't see anything more yet (but there might be something bigger).
// In theory the 11 sectors per track could be up to 13720 bytes big, so 13800 should be enough here.
// In case something bigger appears (e.g. 12 sectors per track), consider shortening GAP 2, GAP 3a, GAP 3B, GAP 4, which take 774 bytes before encoding, 1548 bytes after encoding,
// so if more space for real data would be needed, some adaptive reducing of GAPs sizes could be added (to a point where WD1772 still considers those GAPs to be valid to catch the sync there)
#define MFM_STREAM_SIZE         13800

#define MAKEWORD(A, B)  ( (((uint16_t)A)<<8) | ((uint16_t)B) )

#define HDD_FW_RESPONSE_LEN     12
#define FDD_FW_RESPONSE_LEN     8

#define FW_RESPONSE_LEN_BIGGER  ((HDD_FW_RESPONSE_LEN > FDD_FW_RESPONSE_LEN) ? HDD_FW_RESPONSE_LEN : FDD_FW_RESPONSE_LEN)

#define INBUF_SIZE  (WRITTENMFMSECTOR_SIZE + 8)

#define SYNC_TAG_HDD    0xc050d1c5
#define SYNC_TAG_FDD    0xc0500fdd

#define MAX_CLIENTS     8

#endif
